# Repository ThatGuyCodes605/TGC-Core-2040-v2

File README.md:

# TGC-Core-Pico-v2

## Overview
The **TGC-Core-Pico-v2** is an open-source, IoT-ready hardware development board designed around the Pico architecture (e.g., RP2040). Engineered for high performance, modern connectivity, and sensor [...]

This repository contains the complete set of KiCad EDA files (version 10.0) necessary to view, modify, and manufacture the printed circuit board (PCB).

---

## Key Hardware Features

Based on the schematic and board layout, this board includes the following integrated components and capabilities:

* **Microcontroller:** Pico-compatible architecture featuring a built-in **Temperature Sensor** for internal environmental monitoring.
* **Wireless Connectivity:** Integrated **Wi-Fi** (802.11n) and **Bluetooth** (Classic & BLE), making it perfectly suited for IoT nodes, remote telemetry, and wireless control.
* **Modern Interface:** Upgraded with a **USB Type-C** connector for reliable data transfer and power delivery.
* **Onboard Motion Tracking:** Integrated **ICM-20602** 6-axis MEMS motion tracking device (accelerometer and gyroscope) for robotics, drones, or motion-sensitive applications.
* **Power Regulation:** Onboard **AMS1117-3.3** Low Dropout (LDO) regulator providing a stable 3.3V supply across the board.
* **PCB Specs:** Designed as a 4-layer FR4 board for optimal signal integrity, thermal dissipation, and power routing.

---

## Repository Structure

The project is entirely self-contained within the following native KiCad design files:

| File Name | Description |
| :--- | :--- |
| `TGC-Core-Pico-v2.kicad_pro` | The main **KiCad Project file**. Open this file to load the entire workspace. |
| `TGC-Core-Pico-v2.kicad_sch` | The **Schematic file**. Contains the logical connections, USB-C wiring, wireless modules, regulator, and IMU configuration. |
| `TGC-Core-Pico-v2.kicad_pcb` | The **PCB Layout file**. Contains the physical 4-layer board routing, copper pours, and silkscreen definitions. |
| `image_78bedf.png` | A visual render of the top board design. |

---

## Getting Started

### 1. Viewing and Editing the Hardware
To view or modify the hardware design:
1. Download and install [KiCad EDA](https://www.kicad.org/) (Ensure you are using a modern version compatible with KiCad v10 files).
2. Open the `TGC-Core-Pico-v2.kicad_pro` file.
3. Use the Schematic Editor to view component wiring or the PCB Editor to inspect the board stackup, wireless antenna keep-outs, and routing.

### 2. Manufacturing
You can generate standard manufacturing files (Gerbers, Drill files, BOM, and CPL/Pos files for PCBA) directly from the `TGC-Core-Pico-v2.kicad_pcb` file using KiCad's fabrication output tools.

---

## License

This hardware design and its accompanying documentation are licensed under the **GNU General Public License v3.0 (GPL-3.0-or-later)**.

Summary of your rights under GPLv3:
* You are free to use, study, share, and modify the material.
* If you distribute the work (or a derivative), you must license the whole work under GPLv3 as well (share-alike).
* You must provide source for distributed derivative works and include the GPLv3 license text and copyright notices.

For the full legal text, see the GNU licenses page: https://www.gnu.org/licenses/gpl-3.0.html

Note: To make the change complete, consider adding a `LICENSE` file containing the full GPLv3 text and an explicit copyright line (for example: "Copyright (c) 2026 ThatGuyCodes605"). I can add that file for you if you want.

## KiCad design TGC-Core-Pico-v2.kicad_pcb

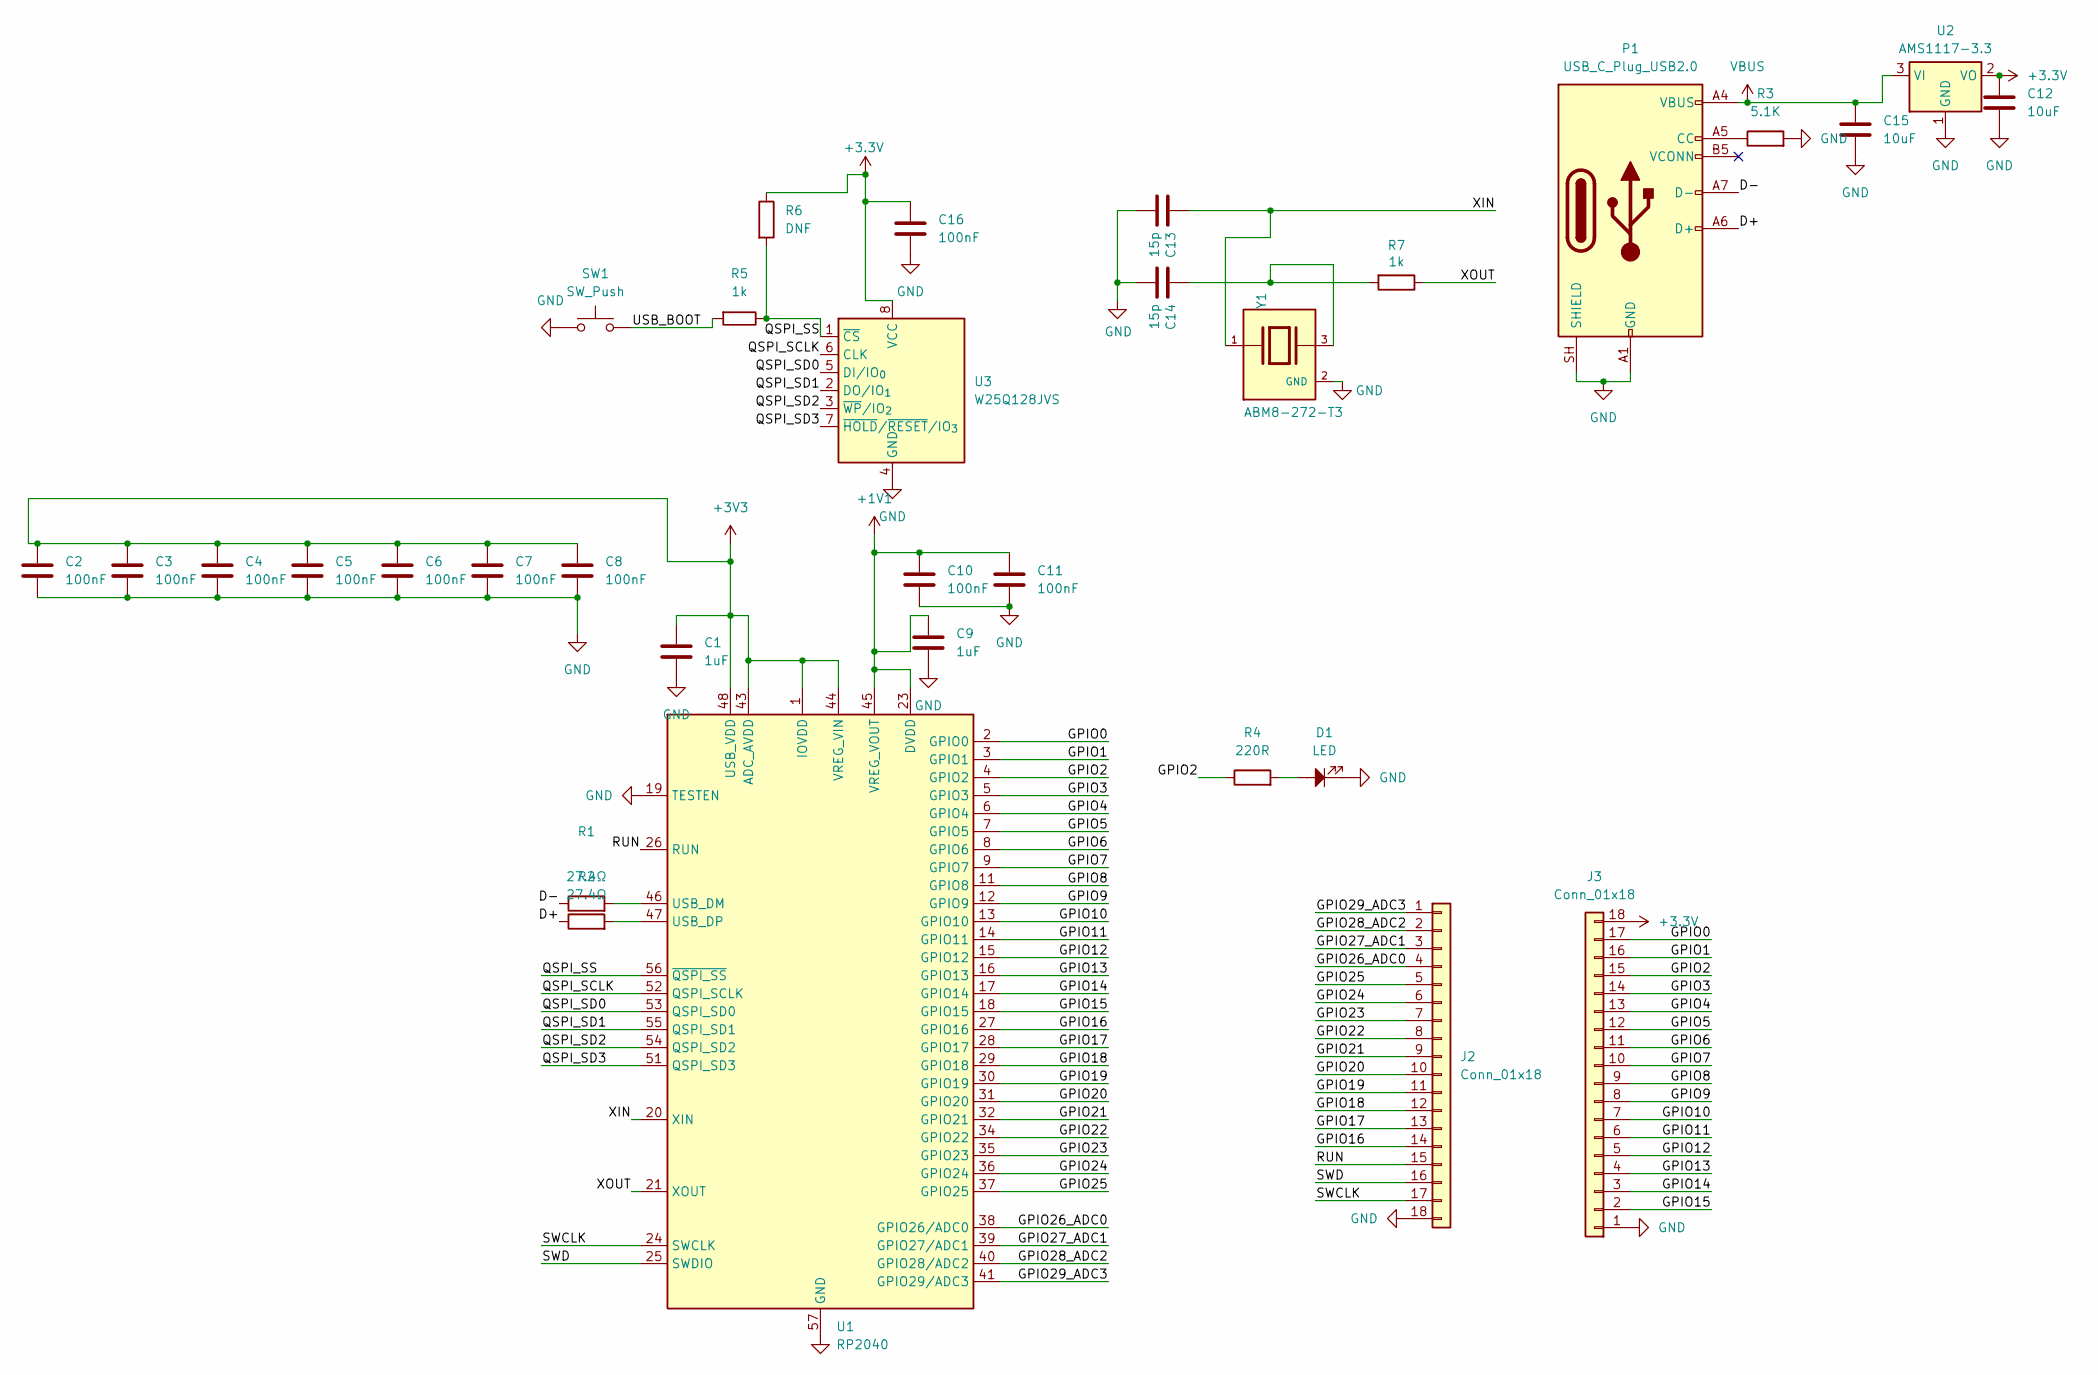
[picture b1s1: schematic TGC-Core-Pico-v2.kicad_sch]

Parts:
C1, C9: 1uF; C_0805_2012Metric
C2, C3, C4, C5, C6, C7, C8, C10, C11, C16: 100nF; C_0805_2012Metric
C12, C15: 10uF; C_0805_2012Metric
C13, C14: 15p; C_0402_1005Metric
D1: LED; LED_1210_3225Metric_Pad1.42x2.65mm_HandSolder
J2, J3: Conn_01x18; PinHeader_1x18_P2.54mm_Vertical
P1: USB_C_Plug_USB2.0; USB_C_Receptacle_HRO_TYPE-C-31-M-12
R1, R2: 27.4Ω; R_0402_1005Metric
R3: 5.1K; R_0402_1005Metric
R4: 220R; R_0402_1005Metric
R5, R7: 1k; R_0402_1005Metric
R6: DNF; R_0402_1005Metric
SW1: SW_Push; SW_SPST_B3U-1000P
U1: RP2040; QFN-56-1EP_7x7mm_P0.4mm_EP3.2x3.2mm
U2: AMS1117-3.3; SOT-223-3_TabPin2
U3: W25Q128JVS; SOIC-8_5.3x5.3mm_P1.27mm
Y1: ABM8-272-T3; XTAL_ABM8-272-T3; PARTREV 07-29-20

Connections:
+1V1: C9.2, C10.1, C11.1, U1.23 (DVDD), U1.45 (VREG_VOUT), U1.50 (DVDD)
+3.3V: C12.1, C16.1, J3.18, R6.1, U2.2 (VO), U3.8 (VCC)
+3V3: C1.2, C2.1, C3.1, C4.1, C5.1, C6.1, C7.1, C8.1, U1.1 (IOVDD), U1.10 (IOVDD), U1.22 (IOVDD), U1.33 (IOVDD), U1.42 (IOVDD), U1.43 (ADC_AVDD), U1.44 (VREG_VIN), U1.48 (USB_VDD), U1.49 (IOVDD)
/D+: P1.A6 (D+), R2.1
/D-: P1.A7 (D-), R1.1
/GPIO0: J3.17, U1.2 (GPIO0)
/GPIO1: J3.16, U1.3 (GPIO1)
/GPIO2: J3.15, R4.1, U1.4 (GPIO2)
/GPIO3: J3.14, U1.5 (GPIO3)
/GPIO4: J3.13, U1.6 (GPIO4)
/GPIO5: J3.12, U1.7 (GPIO5)
/GPIO6: J3.11, U1.8 (GPIO6)
/GPIO7: J3.10, U1.9 (GPIO7)
/GPIO8: J3.9, U1.11 (GPIO8)
/GPIO9: J3.8, U1.12 (GPIO9)
/GPIO10: J3.7, U1.13 (GPIO10)
/GPIO11: J3.6, U1.14 (GPIO11)
/GPIO12: J3.5, U1.15 (GPIO12)
/GPIO13: J3.4, U1.16 (GPIO13)
/GPIO14: J3.3, U1.17 (GPIO14)
/GPIO15: J3.2, U1.18 (GPIO15)
/GPIO16: J2.14, U1.27 (GPIO16)
/GPIO17: J2.13, U1.28 (GPIO17)
/GPIO18: J2.12, U1.29 (GPIO18)
/GPIO19: J2.11, U1.30 (GPIO19)
/GPIO20: J2.10, U1.31 (GPIO20)
/GPIO21: J2.9, U1.32 (GPIO21)
/GPIO22: J2.8, U1.34 (GPIO22)
/GPIO23: J2.7, U1.35 (GPIO23)
/GPIO24: J2.6, U1.36 (GPIO24)
/GPIO25: J2.5, U1.37 (GPIO25)
/GPIO26_ADC0: J2.4, U1.38 (GPIO26/ADC0)
/GPIO27_ADC1: J2.3, U1.39 (GPIO27/ADC1)
/GPIO28_ADC2: J2.2, U1.40 (GPIO28/ADC2)
/GPIO29_ADC3: J2.1, U1.41 (GPIO29/ADC3)
/QSPI_SCLK: U1.52 (QSPI_SCLK), U3.6 (CLK)
/QSPI_SD0: U1.53 (QSPI_SD0), U3.5 (DI/IO_{0})
/QSPI_SD1: U1.55 (QSPI_SD1), U3.2 (DO/IO_{1})
/QSPI_SD2: U1.54 (QSPI_SD2), U3.3 (~WP/IO_{2})
/QSPI_SD3: U1.51 (QSPI_SD3), U3.7 (~HOLD/~RESET/IO_{3})
/QSPI_SS: R5.2, R6.2, U1.56 (~QSPI_SS), U3.1 (~CS)
/RUN: J2.15, U1.26 (RUN)
/SWCLK: J2.17, U1.24 (SWCLK)
/SWD: J2.16, U1.25 (SWDIO)
/USB_BOOT: R5.1, SW1.2
/XIN: C13.1, U1.20 (XIN), Y1.1
/XOUT: R7.1, U1.21 (XOUT)
GND: C1.1, C2.2, C3.2, C4.2, C5.2, C6.2, C7.2, C8.2, C9.1, C10.2, C11.2, C12.2, C13.2, C14.2, C15.2, C16.2, D1.1, J2.18, J3.1, P1.A1 (GND), P1.A12 (GND), P1.B1 (GND), P1.B12 (GND), P1.SH (SHIELD), R3.2, SW1.1, U1.19 (TESTEN), U1.57 (GND), U2.1 (GND), U3.4 (GND), Y1.2 (GND), Y1.4 (GND)
unnamed: C14.1, R7.2, Y1.3
unnamed: D1.2, R4.2
unnamed: P1.A5 (CC), R3.1
unnamed: R1.2, U1.46 (USB_DM)
unnamed: R2.2, U1.47 (USB_DP)
VBUS: C15.1, P1.A4 (VBUS), P1.A9 (VBUS), P1.B4 (VBUS), P1.B9 (VBUS), U2.3 (VI)

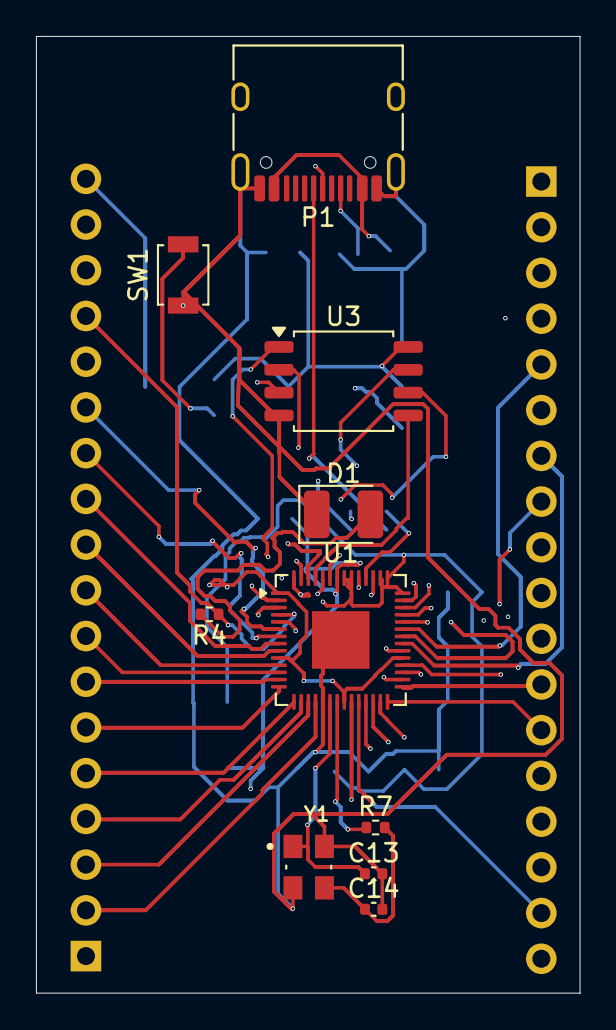
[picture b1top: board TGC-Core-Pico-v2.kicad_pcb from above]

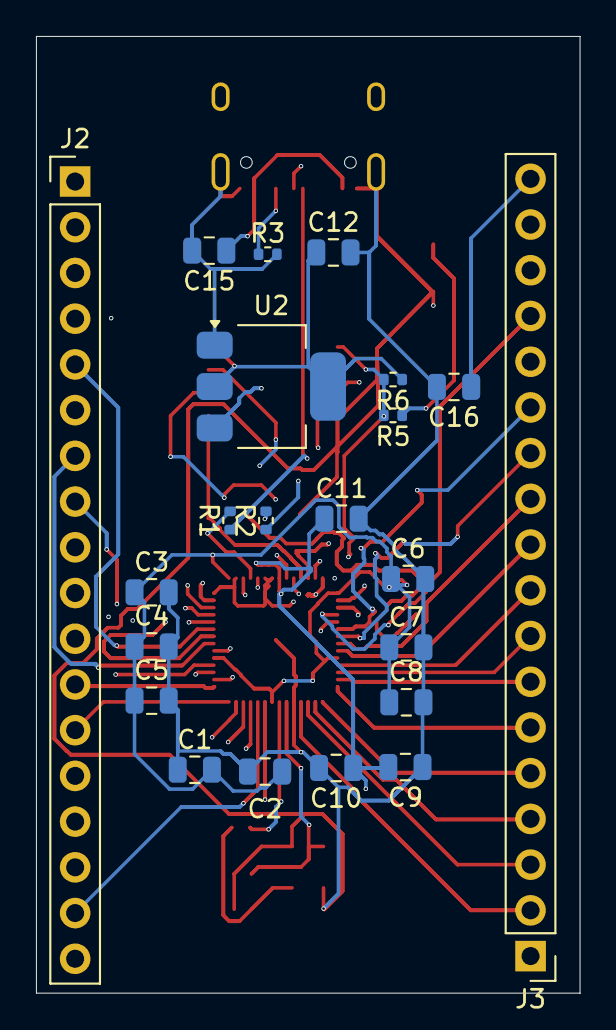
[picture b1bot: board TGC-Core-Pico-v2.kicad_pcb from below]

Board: 4 copper layers, 30.2 x 53.2 mm, 32 parts (22 on the bottom side), 54 nets.

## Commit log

2026-05-31 Revise README for TGC-Core-Pico-v2
    Updated project name and expanded documentation with detailed features, repository structure, and getting started instructions.
2026-05-31 Update README with enhanced board description and features
    Enhanced the overview and key features of the TGC-Core-Pico-v2 board, including updates on wireless connectivity and internal components.
2026-05-31 Add Creative Commons Attribution 4.0 License
    Added the Creative Commons Attribution 4.0 International Public License to the project.
2026-06-07 Change license to GNU GPLv3 in README
2026-06-07 Add GNU General Public License v3
